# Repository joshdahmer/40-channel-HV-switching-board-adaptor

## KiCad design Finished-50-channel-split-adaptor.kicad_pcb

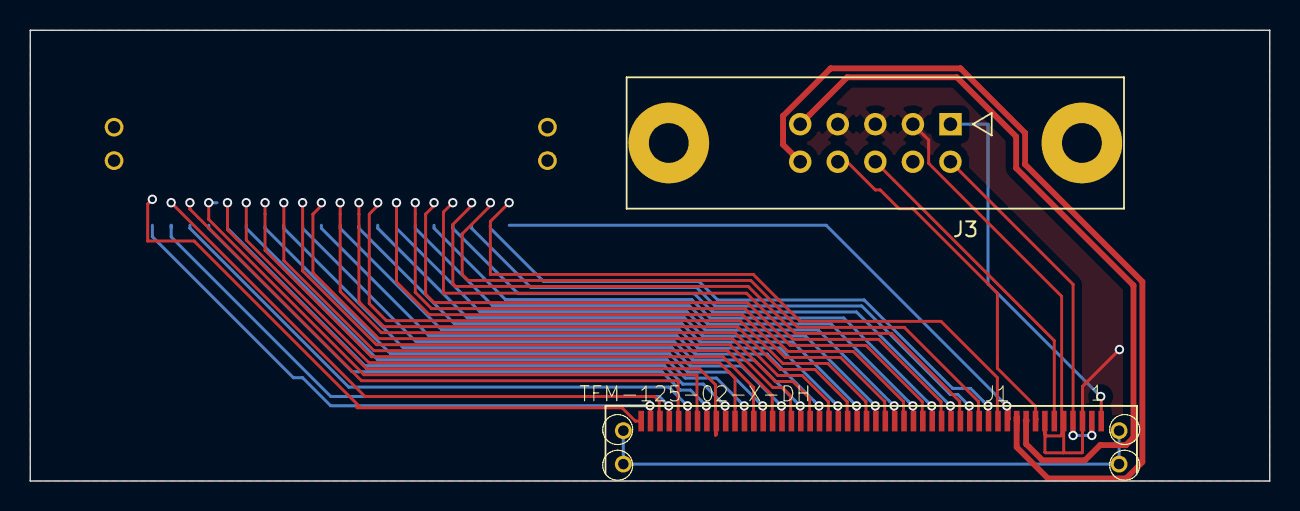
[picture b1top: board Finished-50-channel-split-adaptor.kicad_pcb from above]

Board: 2 copper layers, 83.8 x 30.5 mm, 3 parts (1 on the bottom side), 48 nets.

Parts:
J1: TFM-125-02-X-DH; SFM-125-02-X-DH
J2: TFM-120-02-X-DH
J3: CONN_02X05; he10-10d

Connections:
+3.3V: J1.2, J1.4, J3.2, J3.4
A4/SDA: J1.1, J3.1
A5/SCL: J1.6, J3.6
CHASIS_GND: J1.G1, J1.G2, J1.G3, J1.G4
GND: J1.3, J1.5, J1.7, J3.3, J3.5, J3.7
HV: J1.9, J3.9
HVGND: J1.10, J3.10
HVOUT0: J1.50, J2.1
HVOUT1: J1.49, J2.2
HVOUT2: J1.48, J2.3
HVOUT3: J1.47, J2.4
HVOUT4: J1.46, J2.5
HVOUT5: J1.45, J2.6
HVOUT6: J1.44, J2.7
HVOUT7: J1.43, J2.8
HVOUT8: J1.42, J2.9
HVOUT9: J1.41, J2.10
HVOUT10: J1.40, J2.11
HVOUT11: J1.39, J2.12
HVOUT12: J1.38, J2.13
HVOUT13: J1.37, J2.14
HVOUT14: J1.36, J2.15
HVOUT15: J1.35, J2.16
HVOUT16: J1.34, J2.17
HVOUT17: J1.33, J2.18
HVOUT18: J1.32, J2.19
HVOUT19: J1.31, J2.20
HVOUT20: J1.30, J2.21
HVOUT21: J1.29, J2.22
HVOUT22: J1.28, J2.23
HVOUT23: J1.27, J2.24
HVOUT24: J1.26, J2.25
HVOUT25: J1.25, J2.26
HVOUT26: J1.24, J2.27
HVOUT27: J1.23, J2.28
HVOUT28: J1.22, J2.29
HVOUT29: J1.21, J2.30
HVOUT30: J1.20, J2.31
HVOUT31: J1.19, J2.32
HVOUT32: J1.18, J2.33
HVOUT33: J1.17, J2.34
HVOUT34: J1.16, J2.35
HVOUT35: J1.15, J2.36
HVOUT36: J1.14, J2.37
HVOUT37: J1.13, J2.38
HVOUT38: J1.12, J2.39
HVOUT39: J1.11, J2.40
RST: J1.8, J3.8

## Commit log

2017-05-23 Initial Commit
    New repository
2017-05-23 Gerber files
2017-05-24 Added gitignore and other files
